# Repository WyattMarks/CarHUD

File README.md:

# CarHUD
This is a reflective Car Heads Up Display. It is being actively developed.

The contributors include Wyatt Marks, Emily Moore, and Bobby Foy.

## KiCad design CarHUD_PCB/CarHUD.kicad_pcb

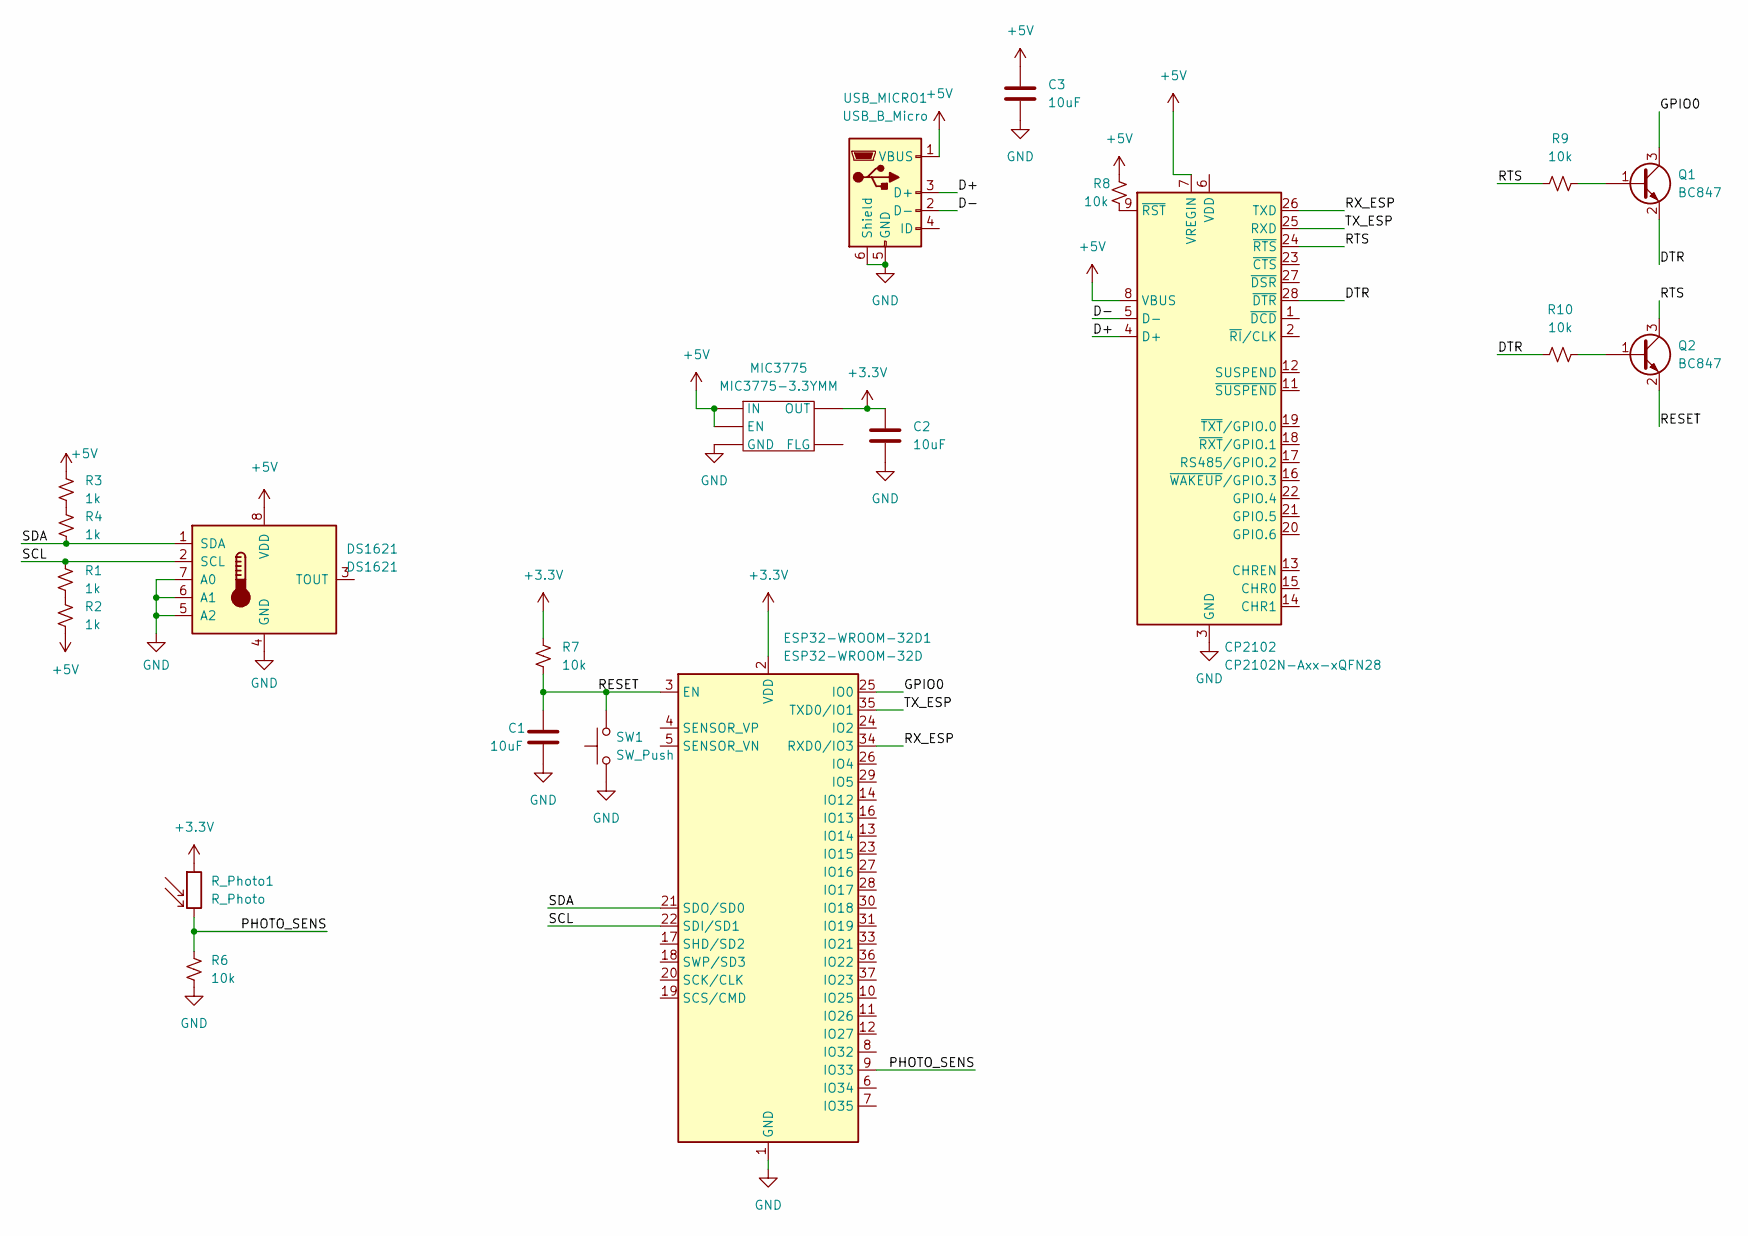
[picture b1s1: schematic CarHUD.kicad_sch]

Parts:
C1, C2, C3: 10uF; C_0603_1608Metric
CP2102: CP2102N-Axx-xQFN28; QFN-28-1EP_5x5mm_P0.5mm_EP3.35x3.35mm
DS1621: DS1621; DIP-8_W7.62mm
ESP32-WROOM-32D1: ESP32-WROOM-32D; ESP32-WROOM-32
MIC3775: MIC3775-3.3YMM; MSOP8-Reg
Q1, Q2: BC847; SOT-523
R1, R2, R3, R4: 1k; R_0603_1608Metric
R6, R7, R8, R9, R10: 10k; R_0603_1608Metric
R_Photo1: R_Photo; R_Axial_DIN0204_L3.6mm_D1.6mm_P2.54mm_Vertical
SW1: SW_Push; SW_SPST_EVPBF
USB_MICRO1: USB_B_Micro; USB_Micro-B_Amphenol_10104110_Horizontal

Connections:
+3V3: C2.1, ESP32-WROOM-32D1.2 (VDD), MIC3775.OUT, R7.1, R_Photo1.1
+5V: C3.1, CP2102.7 (VREGIN), CP2102.8 (VBUS), DS1621.8 (VDD), MIC3775.EN, MIC3775.IN, R2.2, R3.1, R8.2, USB_MICRO1.1 (VBUS)
/D+: CP2102.4 (D+), USB_MICRO1.3 (D+)
/D-: CP2102.5 (D-), USB_MICRO1.2 (D-)
/DTR: CP2102.28 (~DTR), Q1.2 (E), R10.1
/GPIO0: ESP32-WROOM-32D1.25 (IO0), Q1.3 (C)
/PHOTO_SENS: ESP32-WROOM-32D1.9 (IO33), R6.1, R_Photo1.2
/RESET: C1.1, ESP32-WROOM-32D1.3 (EN), Q2.2 (E), R7.2, SW1.2
/RTS: CP2102.24 (~RTS), Q2.3 (C), R9.1
/RX_ESP: CP2102.26 (TXD), ESP32-WROOM-32D1.34 (RXD0/IO3)
/SCL: DS1621.2 (SCL), ESP32-WROOM-32D1.22 (SDI/SD1), R1.1
/SDA: DS1621.1 (SDA), ESP32-WROOM-32D1.21 (SDO/SD0), R4.2
/TX_ESP: CP2102.25 (RXD), ESP32-WROOM-32D1.35 (TXD0/IO1)
GND: C1.2, C2.2, C3.2, CP2102.3 (GND), CP2102.29 (GND), DS1621.4 (GND), DS1621.5 (A2), DS1621.6 (A1), DS1621.7 (A0), ESP32-WROOM-32D1.1 (GND), ESP32-WROOM-32D1.15 (GND), ESP32-WROOM-32D1.38 (GND), ESP32-WROOM-32D1.39 (GND), MIC3775.GND, R6.2, SW1.1, USB_MICRO1.5 (GND), USB_MICRO1.6 (Shield)
unnamed: CP2102.9 (~RST), R8.1
unnamed: Q1.1 (B), R9.2
unnamed: Q2.1 (B), R10.2
unnamed: R1.2, R2.1
unnamed: R3.2, R4.1

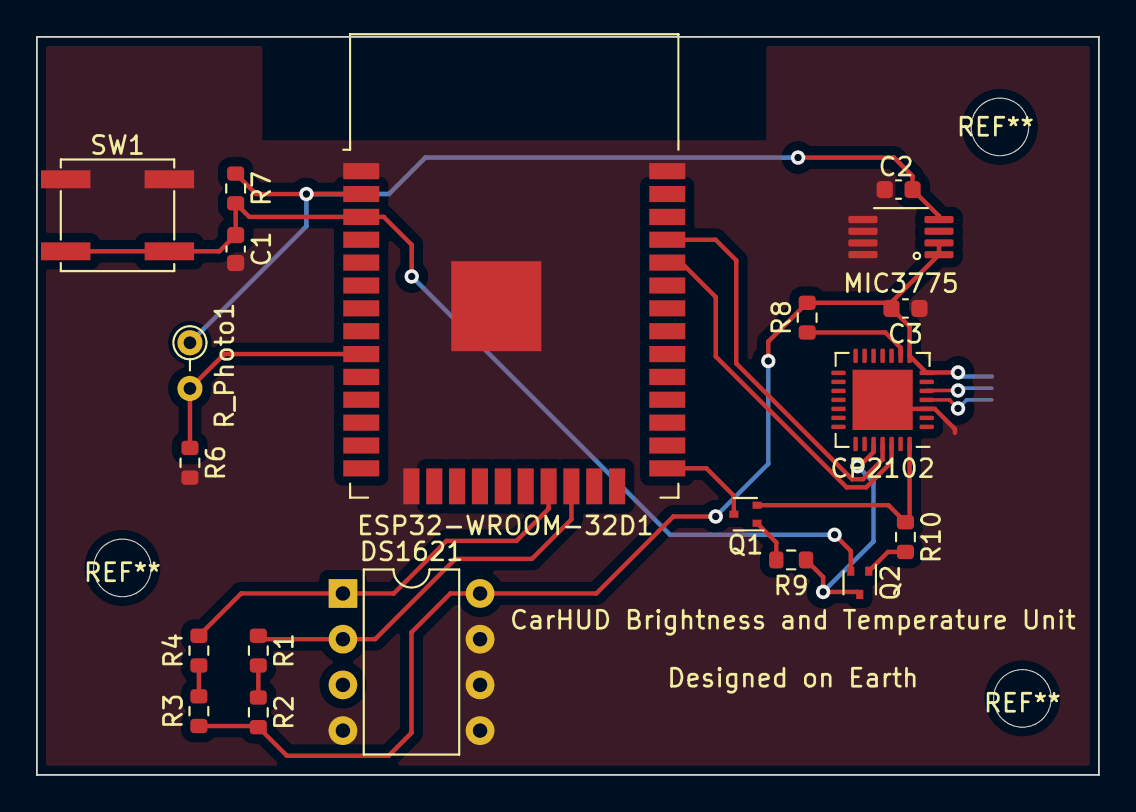
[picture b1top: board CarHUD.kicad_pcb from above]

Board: 2 copper layers, 59.0 x 41.0 mm, 21 parts (1 on the bottom side), 19 nets.

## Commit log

2022-05-16 Sensor PCB Created
2022-05-16 Wrote class to handle GPS data
2022-05-16 Removed two debug prints
2022-05-16 Initial PyGame code, displays GPS data
2022-05-16 Added beginning of OBD code. Untested as of RN
2022-05-20 Create initial firmware for sensor board. Only reading brightness currently
2022-05-22 Got brightness to display something meaningful
2022-05-22 Forgot to commit board module
2022-05-22 hardcode board port
2022-05-22 Get commands handled correctly, finally
2022-06-21 Refactor OBD connection
2022-06-21 Change screen layout. Add a gauge graphic
2022-06-22 Fixed PCB temperature reading. Update code to support it
